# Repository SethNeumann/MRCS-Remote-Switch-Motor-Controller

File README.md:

# REPO NAME: MRCS-Remote-Switch-Motor-Controller

The Remote Stall Motor Controller is designed to mount on a Circuitron(r) Tortoise slow motion switch machine and provides bi-polar control with a single logic level line, such as provided by a cpNode, IOX16/32, SMINI, DOUT, or SPST toggle switch. The RSMC can also be used to control the MP1 switch motor.

## License: Creative Commons Attribution-NonCommercial-ShareAlike

MRCS-Remote-Switch-Motor-Controller

The Remote Stall Motor Controller is designed to mount on a Circuitron(r) Tortoise slow motion switch machine and provides bi-polar control with a single logic level line, such as provided by a cpNode, IOX16/32, SMINI, DOUT, or SPST toggle switch. The RSMC can also be used to control the MP1 switch motor.

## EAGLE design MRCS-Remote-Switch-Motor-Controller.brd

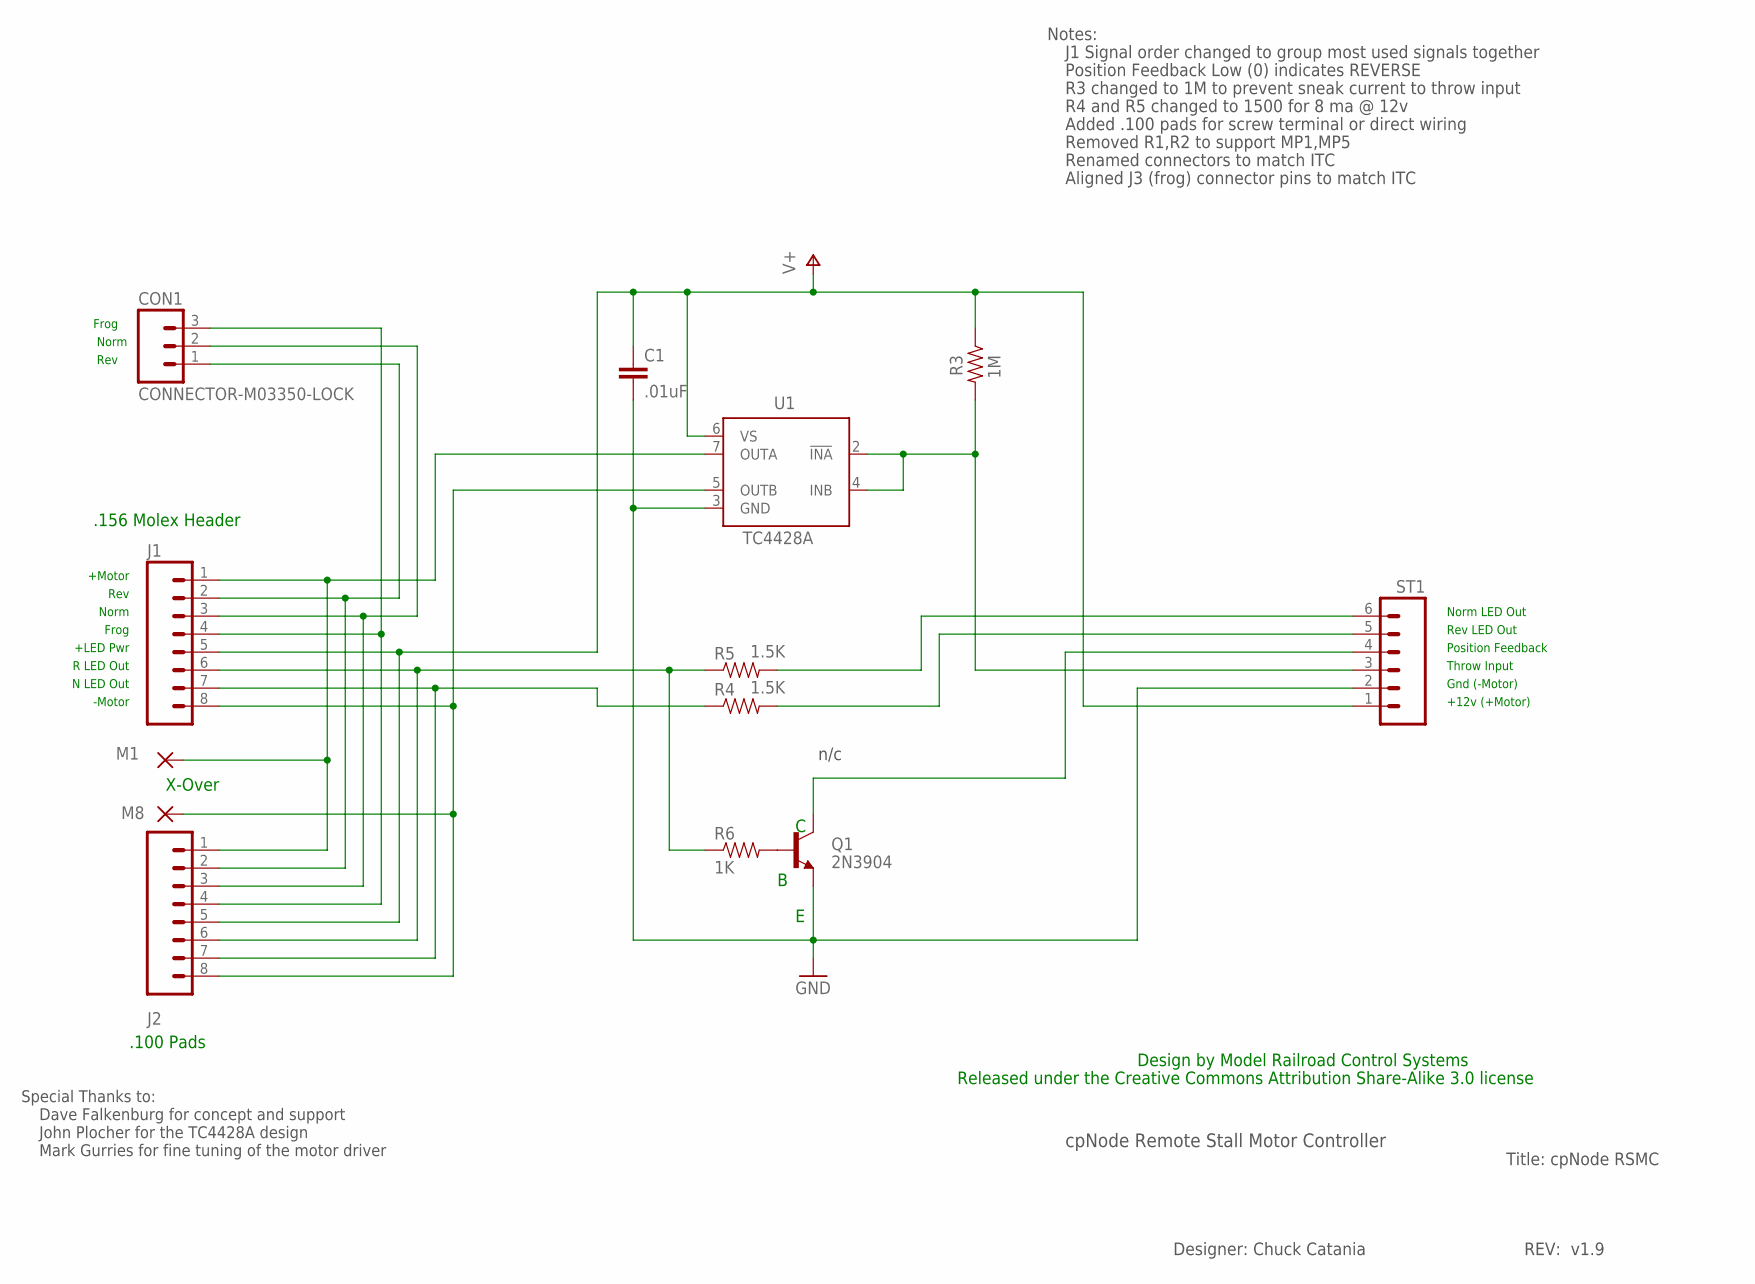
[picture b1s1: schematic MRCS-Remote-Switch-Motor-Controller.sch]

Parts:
C1: .01uF; CAP-PTH-SMALLEZ
CON1: CONNECTOR-M03350-LOCK; 1751251
J1: J1; KK-156-8-F
J2: J2; 1X08_PIN1_NO_SILK
M1, M8: WIREPAD2,54/1,1; 2,54/1,1
Q1: 2N3904; TO-92-MS013
R3: 1M; AXIAL-0.4-RES
R4, R5: 1.5K; AXIAL-0.4-RES
R6: 1K; AXIAL-0.4-RES
ST1: M06LOCK; 1X06_LOCK
U1: TC4428A; DIL08

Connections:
FROG: CON1.3, J1.4, J2.4
GND: C1.2, Q1.1 (E), ST1.2, U1.3 (GND)
M+: J1.1, J2.1, M1.1, U1.7 (OUTA)
M-: J1.8, J2.8, M8.1, U1.5 (OUTB)
unnamed: Q1.3 (C), ST1.4
unnamed: R4.P$2 (2), ST1.5
unnamed: Q1.2 (B), R6.P$2 (2)
unnamed: R5.P$2 (2), ST1.6
unnamed: R3.P$2 (2), ST1.3, U1.2 (!INA), U1.4 (INB)
N-LED: J1.7, J2.7, R4.P$1 (1)
NORM: CON1.2, J1.3, J2.3
R-LED: J1.6, J2.6, R5.P$1 (1), R6.P$1 (1)
REV: CON1.1, J1.2, J2.2
V+: C1.1, J1.5, J2.5, R3.P$1 (1), ST1.1, U1.6 (VS)

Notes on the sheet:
Norm
Rev
+12v (+Motor)
Gnd (-Motor)
Norm LED Out
Rev LED Out
Frog
+Motor
-Motor
Throw Input
+LED Pwr
R LED Out
N LED Out
.156 Molex Header
Position Feedback
cpNode Remote Stall Motor Controller
Title: cpNode RSMC
Designer: Chuck Catania
REV: v1.9
n/c
Special Thanks to:
John Plocher for the TC4428A design
Dave Falkenburg for concept and support
Mark Gurries for fine tuning of the motor driver
Notes:
Position Feedback Low (0) indicates REVERSE
R4 and R5 changed to 1500 for 8 ma @ 12v
J1 Signal order changed to group most used signals together
R3 changed to 1M to prevent sneak current to throw input
Frog
.100 Pads
Added .100 pads for screw terminal or direct wiring
X-Over
Removed R1,R2 to support MP1,MP5
Renamed connectors to match ITC
Aligned J3 (frog) connector pins to match ITC
Released under the Creative Commons Attribution Share-Alike 3.0 license
Design by Model Railroad Control Systems

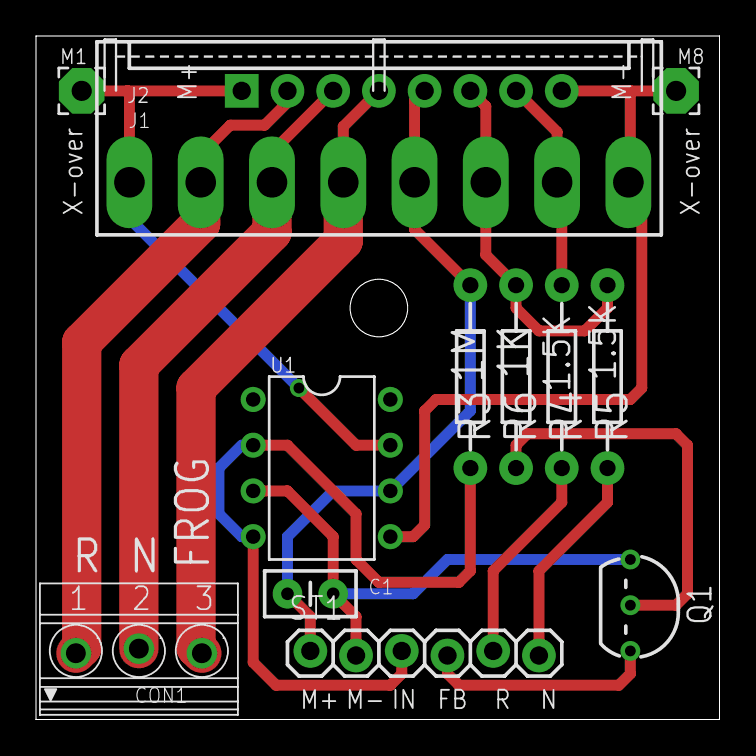
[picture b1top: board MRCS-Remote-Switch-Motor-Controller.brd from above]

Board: 2 copper layers, 38.0 x 38.0 mm, 15 parts (0 on the bottom side), 14 nets.

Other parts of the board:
U$1: MRCSLOGOBTM
U$2: CA-PROP65WARNING

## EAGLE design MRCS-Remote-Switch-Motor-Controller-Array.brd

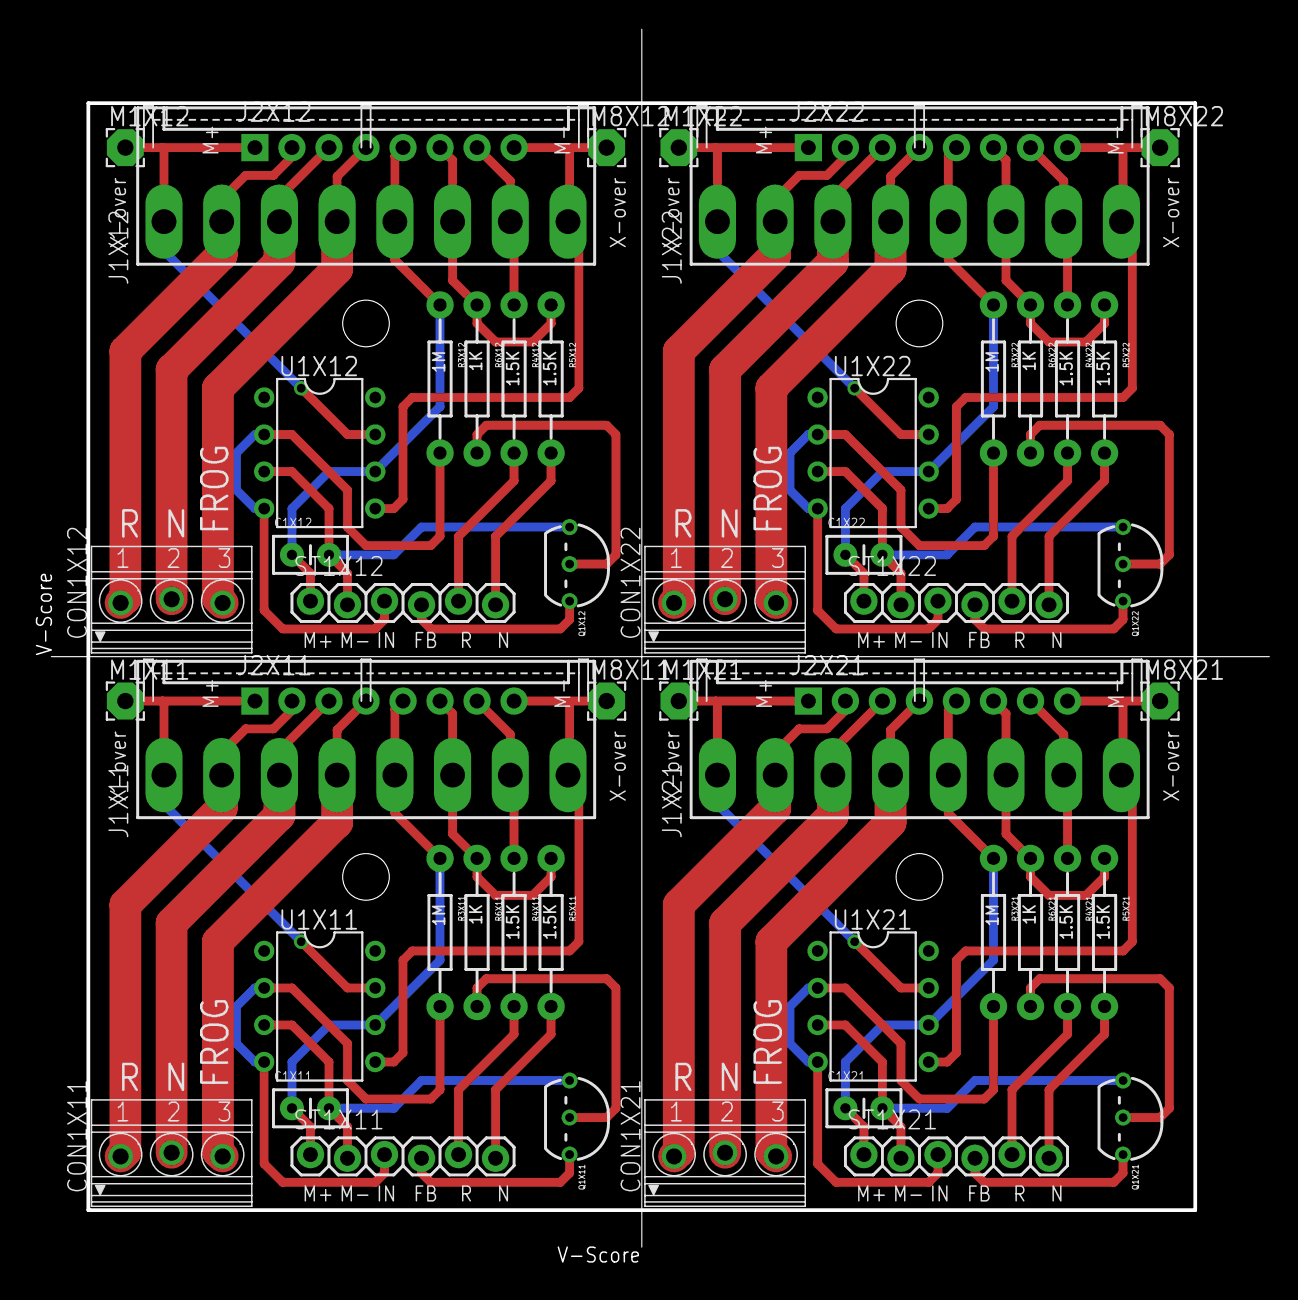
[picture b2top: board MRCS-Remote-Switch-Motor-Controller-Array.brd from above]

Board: 2 copper layers, 84.8 x 84.9 mm, 60 parts (0 on the bottom side), 56 nets.

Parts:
C1X11, C1X12, C1X21, C1X22: .01uF; CAP-PTH-SMALLEZ
CON1X11, CON1X12, CON1X21, CON1X22: CONNECTOR-M03350-LOCK; 1751251
J1X11, J1X12, J1X21, J1X22: J1; KK-156-8-F
J2X11, J2X12, J2X21, J2X22: J2; 1X08_PIN1_NO_SILK
M1X11, M1X12, M1X21, M1X22, M8X11, M8X12, M8X21, M8X22: WIREPAD2,54/1,1; 2,54/1,1
Q1X11, Q1X12, Q1X21, Q1X22: 2N3904; TO-92-MS013
R3X11, R3X12, R3X21, R3X22: 1M; AXIAL-0.4-RES
R4X11, R4X12, R4X21, R4X22, R5X11, R5X12, R5X21, R5X22: 1.5K; AXIAL-0.4-RES
R6X11, R6X12, R6X21, R6X22: 1K; AXIAL-0.4-RES
ST1X11, ST1X12, ST1X21, ST1X22: 1X06_LOCK
U1X11, U1X12, U1X21, U1X22: TC4428A; DIL08
U$1X11, U$1X12, U$1X21, U$1X22: MRCSLOGOBTM
U$2X11, U$2X12, U$2X21, U$2X22: CA-PROP65WARNING

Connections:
FROGX11: CON1X11.3, J1X11.4, J2X11.4
FROGX12: CON1X12.3, J1X12.4, J2X12.4
FROGX21: CON1X21.3, J1X21.4, J2X21.4
FROGX22: CON1X22.3, J1X22.4, J2X22.4
GNDX11: C1X11.2, Q1X11.1, ST1X11.2, U1X11.3
GNDX12: C1X12.2, Q1X12.1, ST1X12.2, U1X12.3
GNDX21: C1X21.2, Q1X21.1, ST1X21.2, U1X21.3
GNDX22: C1X22.2, Q1X22.1, ST1X22.2, U1X22.3
M+X11: J1X11.1, J2X11.1, M1X11.1, U1X11.7
M+X12: J1X12.1, J2X12.1, M1X12.1, U1X12.7
M+X21: J1X21.1, J2X21.1, M1X21.1, U1X21.7
M+X22: J1X22.1, J2X22.1, M1X22.1, U1X22.7
M-X11: J1X11.8, J2X11.8, M8X11.1, U1X11.5
M-X12: J1X12.8, J2X12.8, M8X12.1, U1X12.5
M-X21: J1X21.8, J2X21.8, M8X21.1, U1X21.5
M-X22: J1X22.8, J2X22.8, M8X22.1, U1X22.5
unnamed: Q1X11.3, ST1X11.4
unnamed: Q1X12.3, ST1X12.4
unnamed: Q1X21.3, ST1X21.4
unnamed: Q1X22.3, ST1X22.4
unnamed: R4X11.P$2, ST1X11.5
unnamed: R4X12.P$2, ST1X12.5
unnamed: R4X21.P$2, ST1X21.5
unnamed: R4X22.P$2, ST1X22.5
unnamed: Q1X11.2, R6X11.P$2
unnamed: Q1X12.2, R6X12.P$2
unnamed: Q1X21.2, R6X21.P$2
unnamed: Q1X22.2, R6X22.P$2
unnamed: R5X11.P$2, ST1X11.6
unnamed: R5X12.P$2, ST1X12.6
unnamed: R5X21.P$2, ST1X21.6
unnamed: R5X22.P$2, ST1X22.6
unnamed: R3X11.P$2, ST1X11.3, U1X11.2, U1X11.4
unnamed: R3X12.P$2, ST1X12.3, U1X12.2, U1X12.4
unnamed: R3X21.P$2, ST1X21.3, U1X21.2, U1X21.4
unnamed: R3X22.P$2, ST1X22.3, U1X22.2, U1X22.4
N-LEDX11: J1X11.7, J2X11.7, R4X11.P$1
N-LEDX12: J1X12.7, J2X12.7, R4X12.P$1
N-LEDX21: J1X21.7, J2X21.7, R4X21.P$1
N-LEDX22: J1X22.7, J2X22.7, R4X22.P$1
NORMX11: CON1X11.2, J1X11.3, J2X11.3
NORMX12: CON1X12.2, J1X12.3, J2X12.3
NORMX21: CON1X21.2, J1X21.3, J2X21.3
NORMX22: CON1X22.2, J1X22.3, J2X22.3
R-LEDX11: J1X11.6, J2X11.6, R5X11.P$1, R6X11.P$1
R-LEDX12: J1X12.6, J2X12.6, R5X12.P$1, R6X12.P$1
R-LEDX21: J1X21.6, J2X21.6, R5X21.P$1, R6X21.P$1
R-LEDX22: J1X22.6, J2X22.6, R5X22.P$1, R6X22.P$1
REVX11: CON1X11.1, J1X11.2, J2X11.2
REVX12: CON1X12.1, J1X12.2, J2X12.2
REVX21: CON1X21.1, J1X21.2, J2X21.2
REVX22: CON1X22.1, J1X22.2, J2X22.2
V+X11: C1X11.1, J1X11.5, J2X11.5, R3X11.P$1, ST1X11.1, U1X11.6
V+X12: C1X12.1, J1X12.5, J2X12.5, R3X12.P$1, ST1X12.1, U1X12.6
V+X21: C1X21.1, J1X21.5, J2X21.5, R3X21.P$1, ST1X21.1, U1X21.6
V+X22: C1X22.1, J1X22.5, J2X22.5, R3X22.P$1, ST1X22.1, U1X22.6

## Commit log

2020-10-01 initial commit
    initial commit
2020-10-01 Update INFO
2020-10-01 added description from MRCS website
2020-10-01 added content from MRCS website
2020-10-01 cleanup
2020-10-01 moved to github
    moved to GitHub
2020-12-20 minior changes to labels
    changes for legibility
2020-12-24 Added work files to gitignore and label changes
    Added work files to gitignore and made labels on board 56 mil rather than 32 so they can be read more easily
2021-01-02 Updated Documentation and created pdf
    documentation
2025-01-02 adds MP4 MP10
    long overdue update of RSMC instructions, corrects input terminals, adds MP4, MP10. Format changes
2025-01-02 Delete RSMC Instructions 1_9.pdf
    removed obsolete version
2026-01-17 updated documentation
    1) V2_2 only showed title page
    2) Added update information for MP1/4/10

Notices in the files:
parts and their libraries:
SparkFun-Passives: Licensing: CC v3.0 Share-Alike You are welcome to use this library for commercial purposes.
